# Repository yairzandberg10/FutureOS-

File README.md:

# FutureOS

A custom Android-based OS for a **keys-only feature phone** — no touchscreen anywhere. Base: Android 12 (SDK 31), target device: 640×960px keypad phone (T9 numeric keypad, `\*`/`#`, D-pad nav). Every screen across every app is operable by keypad focus traversal and numeric shortcuts.

Since there's no custom ROM, "System UI" (status bar, lock screen, control center, notification center) is implemented by [FutureUI](FutureUI/) as a set of `AccessibilityService` overlays — the practical way to build a custom system shell on stock Android 12. Design language: dark/glass, Material Symbols Rounded, gradient accents.

## Apps

|Folder|App name|Package|Role|
|-|-|-|-|
|[FutureUI](FutureUI/)|FutureUI|`com.future.futureui`|System UI — status bar, lock screen, control center, notification center|
|[SystemUI](SystemUI/)|System UI|`com.android.sistemui`|A second, parallel implementation of the System UI role — the same six `AccessibilityService`s as FutureUI, plus Do-Not-Disturb scheduling. Not installed on the test device; see the note below|
|[FutureLauncher](FutureLauncher/)|מסך הבית|`com.future.futurelauncher`|Home screen / launcher|
|[Settings](Settings/)|הגדרות|`com.future.settings`|System settings|
|[dialer](dialer/)|טלפון|`com.future.dialer`|Phone dialer|
|[Messages](Messages/)|הודעות|`com.future.messages`|SMS messaging|
|[notes](notes/)|פתקים|`com.future.notes`|Notes|
|[Tasks](Tasks/)|משימות|`com.future.tasks`|Task management - to-do list with priorities|
|[Bluetooth](Bluetooth/)|בלוטוס|`com.future.bluetooth`|Bluetooth device manager - scan, pair, unpair|
|[Calendar](Calendar/)|לוח שנה|`com.future.calendar`|Hebrew calendar, Daf Yomi, location-based zmanim|
|[Contact](Contact/)|אנשי קשר|`com.future.contact`|Contacts|
|[Navigation](Navigation/)|ניווט ותחבורה|`com.future.navigation`|Driving navigation \& public-transit journey planner|
|[Files](Files/)|קבצים|`com.future.files`|File browser|
|[Keyboard](Keyboard/)|מקלדת|`com.future.keyboard`|System-wide T9 predictive text input method|
|[Gallery](Gallery/)|גלריה|`com.future.gallery`|Photo/video gallery|
|[Camera](Camera/)|מצלמה|`com.future.camera`|Camera - live preview, capture, flash, front/back switch|
|[Music](Music/)|מוזיקה|`com.future.music`|Local music player|
|[Sfarim](Sfarim/)|בלכתך בדרך|`com.future.sfarim`|Torah text library|
|[Terminal](Terminal/)|טרמינל|`com.future.terminal`|Root shell terminal|
|[Tools](Tools/)|כלים|`com.future.tools`|Unit converter, QR/text scanner, quick notes, random picker and other small utilities|
|[Flashlight](Flashlight/)|פנס|`com.future.flashlight`|Standalone flashlight — the duplicate inside Tools was removed; FutureUI keeps a torch toggle in the control center, which is the system shell, not a second app|
|[Recorder](Recorder/)|רשמקול|`com.future.recorder`|Voice recorder — records in a foreground service (keeps going with the screen off), live level bars, pause/resume, playback with key seeking, rename/share/delete from the Options menu|
|[Calculator](Calculator/)|מחשבון|`com.future.calculator`|Calculator|
|[Clock](Clock/)|שעון|`com.future.clock`|Alarms, world clock, stopwatch, timer|
|[Fitness](Fitness/)|כושר|`com.future.fitness`|Workout tracking, Bluetooth heart-rate monitor|
|[Remote](Remote/)|שלט|`com.future.remote`|Universal infrared remote (non-TV devices: A/C, fan, audio, custom)|
|[Guide](Guide/)|מדריך למשתמש|`com.future.guide`|On-device user guide for every app|
|[Assistant](Assistant/)|עוזר קולי|`com.future.assistant`|Voice assistant - also opens on a global double-press of OK, see FutureUI|
|[Translate](Translate/)|תרגום|`com.future.translate`|On-device translation (ML Kit), language download for offline use, conversation mode|
|[Wallpapers](Wallpapers/)|רקעים|`com.future.wallpapers`|Wallpaper picker (online catalog). No launcher icon: opens from "Wallpaper" in the launcher's edit mode|

[Frixa](Frixa/) (`com.future.frixa`, recipe catalog and nearby grocery stores) also lives in this repo but is **not part of the system**: it is not in the launcher's built-in app list (`FutureLauncher/DefaultApps.kt`), has no page in the Guide, and holds none of the FutureOS signature permissions.

Two more top-level folders are not standalone apps: [SharedKeypadNav](SharedKeypadNav/) is a shared Gradle library module (`com.future.sharednav`) that **all 30** apps above depend on for D-pad focus handling, T9 digit mapping, and the cross-app design system (colors, spacing, type scale) — see [`SharedKeypadNav/README.md`](SharedKeypadNav/README.md), which is also the canonical design-system reference for this project. [hardware](hardware/) holds CAD files (Onshape motherboard keep-out volumes, an OpenSCAD case/keycap model) for the target device, a Qin F22 Pro.

Each app is a standalone Android Studio project (its own `build.gradle.kts`/`settings.gradle.kts`) living in its own top-level folder here.

## Notes

* `Sfarim/tools/output/sefaria.db` (Torah-text database, ~1.55GB / 6,211 books) is present on disk but **not** tracked in this repo's git — GitHub blocks files over 100MB. It is built directly from Sefaria's public sources via `Sfarim/tools/build_library.py`; see `Sfarim/README.md` for the exact rebuild command. `Sfarim/tools/output/reassemble_sefaria_db.sh` documents an earlier, abandoned plan to split/reassemble a pre-built ~2.1GB copy — no longer needed now that the DB is built from source, but the script is left in place for reference.
* This repo is a fresh consolidation of the individual app projects (no prior per-app git history was carried over).
* **[FutureUI](FutureUI/) and [SystemUI](SystemUI/) both implement the System UI role, and only one of them can be active at a time.** Both declare the same five services (the separate `LockScreenAccessibilityService` was removed on 2026-09-24; FutureUI's lock screen now runs inside its existing services - see `FutureUI/.../lockscreen/` and `LockSettingsActivity` - so a leftover `LockScreenAccessibilityService` entry in `enabled_accessibility_services` on a device is stale and can be removed) — `StatusBarAccessibilityService`, `NotificationCenterAccessibilityService`, `ControlCenterAccessibilityService`, `MediaControlService`, `HeadsUpNotificationService` — under different package names (`com.future.futureui` vs `com.android.sistemui`; the latter is spelled "sistemui" because `com.android.systemui` is a reserved system package and cannot be installed). Enabling both sets of `AccessibilityService`s would make two overlay stacks compete for the same key events, and the status bar service in particular swallows `KEYCODE_MENU`/`KEYCODE_SETTINGS` system-wide, so a duplicate would break the Options key everywhere. On the `F22 Pro` test device only FutureUI is installed and its three overlay services are the ones enabled. Which of the two is intended to win long-term is not recorded anywhere in this repo.

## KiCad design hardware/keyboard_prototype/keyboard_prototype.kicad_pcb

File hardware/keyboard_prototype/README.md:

# FutureOS Keyboard Prototype - מה יש כאן ואיך מזמינים

אב-טיפוס USB של מקלדת FutureOS: ‏21 מקשים, מטריצה 5×5 ותאורה אחורית. הלוח נשלט על ידי XIAO RP2040 **לבדיקה בלבד**, וה-XIAO אינו חלק מהחומרה הסופית של FutureOS Regular.

## הקבצים

| קובץ | מה זה |
|---|---|
| `keyboard_prototype.kicad_pro` | הפרויקט. פותחים אותו ב-KiCad 10 |
| `keyboard_prototype_schematic.pdf` | הסכמה |
| `fab/keyboard_prototype_gerbers.zip` | **הקובץ שמעלים למפעל** (לוח) |
| `fab/BOM_JLCPCB.csv`, `fab/CPL_JLCPCB.csv` | קבצים להרכבת הרכיבים במפעל |
| `fab/keyboard_prototype.step` | מודל תלת-ממדי, להכנסה לגוף ב-CAD |
| `render/pcb_top.png`, `pcb_bottom.png`, `pcb_3d.png` | תמונות של הלוח |
| `firmware/` | הקושחה ל-XIAO וקובץ מיפוי המקשים ל-Android |
| `SPEC.md` | המפרט המאושר |
| `tools/design.py` + `build.sh` | מחולל פרמטרי: משנים את `design.py` ומריצים `./build.sh` |

## הזמנה מ-JLCPCB (10 לוחות)

1. ב-jlcpcb.com בוחרים **Order now** ומעלים את `fab/keyboard_prototype_gerbers.zip`.
2. בוחרים את ההגדרות: 2 שכבות, **עובי 1.0 מ"מ**, כמות 10, וכל השאר בברירת מחדל.
3. מסמנים **PCB Assembly**, צד **Top**, ומעלים את `BOM_JLCPCB.csv` ואת `CPL_JLCPCB.csv`.
4. במסך ה-preview בודקים שכל רכיב יושב על הפדים שלו. **כדאי לבדוק במיוחד את כיוון הדיודות והנורות.** אם משהו מסובב, מתקנים את הסיבוב שם, בממשק של JLC.
5. את ה-XIAO RP2040 קונים בנפרד (Seeed, כ-5 דולר ליחידה). המפעל לא מרכיב אותו.

## הרכבה ידנית (אחרי שהלוחות מגיעים)

1. **ה-XIAO**: מולחם שטוח בצד האחורי, כשהרכיבים שלו פונים החוצה וה-USB-C פונה לקצה התחתון, בהתאם לסימון ה-"USB-C" על הלוח. מלחימים רק את 14 הפדים שבצדדים, ולא את הפדים שמתחתיו.
2. **JP1**: מחברים את שני חצאי הגשר בטיפת בדיל. בלי זה התאורה לא תדלק מה-USB.
3. **J1 (FPC)** לא נדרש לבדיקה עם ה-XIAO. **לא מחברים כבל FPC כשה-XIAO מולחם.**

## הפעלה

1. מחזיקים את כפתור BOOT ב-XIAO ומחברים אותו למחשב. מופיע כונן בשם RPI-RP2.
2. גוררים לכונן קובץ UF2 של CircuitPython ל-XIAO RP2040 מאתר circuitpython.org. אחרי זה מופיע כונן בשם CIRCUITPY.
3. מעתיקים לכונן את `firmware/boot.py` ואת `firmware/code.py`, ומנתקים ומחברים מחדש.
4. במכשיר Android עם root, מתקינים את `firmware/Vendor_1209_Product_0001.kl` לפי ההוראות שבראש הקובץ.
5. מחברים את המקלדת לטלפון דרך OTG.

## מה לבדוק (תכתוב לי את התוצאות)

- כל 21 המקשים: כל מקש שולח את הקוד שכתוב בטבלה ב-`SPEC.md`.
- לחיצה על שני מקשים יחד מזהה את שניהם, בלי "רפאים".
- התאורה נדלקת בלחיצה ונכבית אחרי 8 שניות.

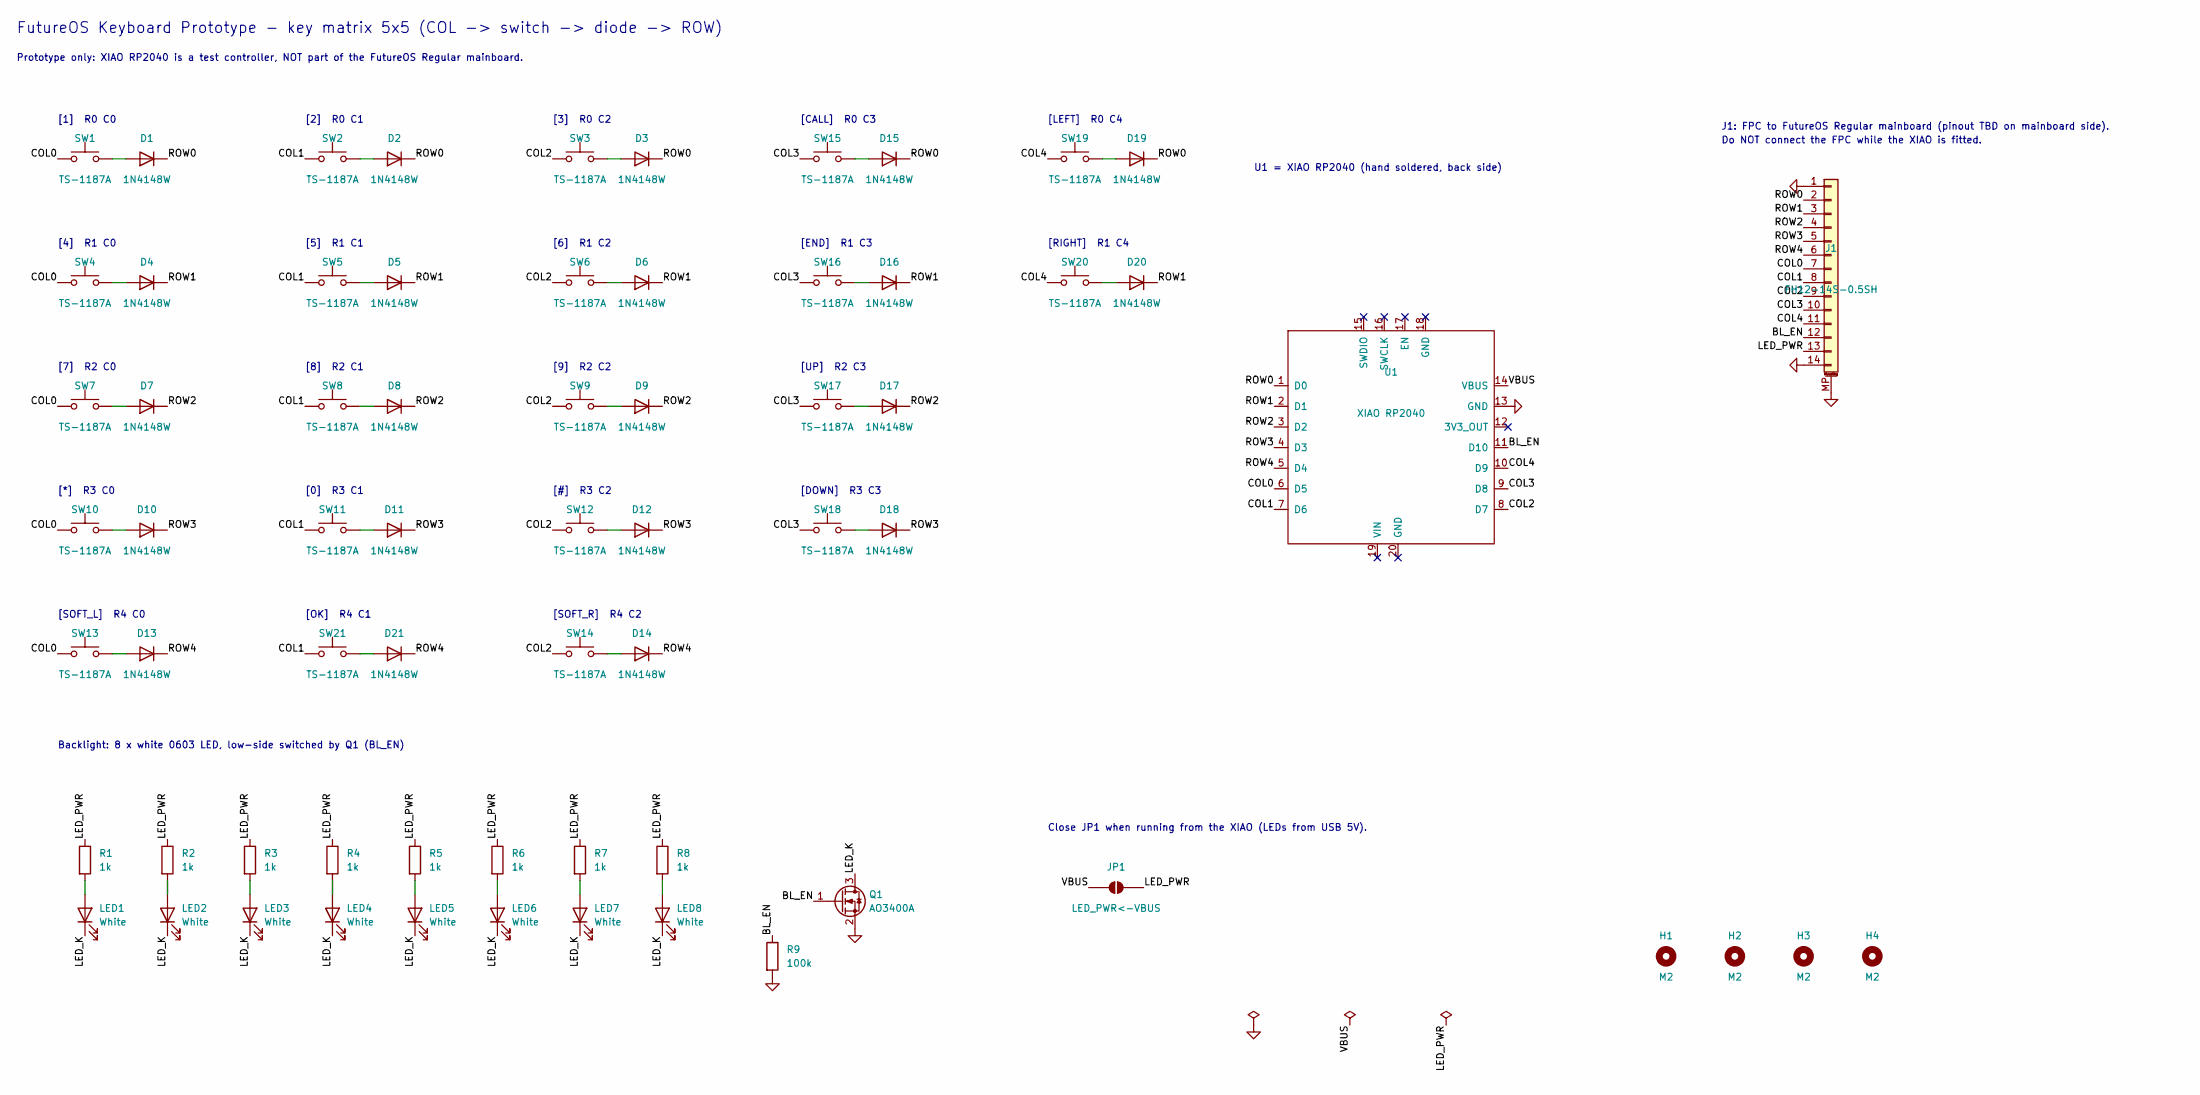
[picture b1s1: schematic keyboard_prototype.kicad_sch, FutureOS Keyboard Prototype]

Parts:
D1, D2, D3, D4, D5, D6, D7, D8, D9, D10, D11, D12, D13, D14, D15, D16, D17, D18, D19, D20, D21: 1N4148W; D_SOD-123
H1, H2, H3, H4: M2; MountingHole_2.2mm_M2
J1: FH12-14S-0.5SH; Hirose_FH12-14S-0.5SH_1x14-1MP_P0.50mm_Horizontal
JP1: LED_PWR<-VBUS; SolderJumper-2_P1.3mm_Open_Pad1.0x1.5mm
LED1, LED2, LED3, LED4, LED5, LED6, LED7, LED8: White; LED_0603_1608Metric
Q1: AO3400A; SOT-23
R1, R2, R3, R4, R5, R6, R7, R8: 1k; R_0603_1608Metric
R9: 100k; R_0603_1608Metric
SW1, SW2, SW3, SW4, SW5, SW6, SW7, SW8, SW9, SW10, SW11, SW12, SW13, SW14, SW15, SW16, SW17, SW18, SW19, SW20, SW21: TS-1187A; SW_Push_1P1T_XKB_TS-1187A
U1: XIAO RP2040; XIAO-RP2040-SMD

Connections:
/BL_EN: J1.12, Q1.1 (G), R9.1, U1.11 (D10)
/COL0: J1.7, SW1.1, SW4.1, SW7.1, SW10.1, SW13.1, U1.6 (D5)
/COL1: J1.8, SW2.1, SW5.1, SW8.1, SW11.1, SW21.1, U1.7 (D6)
/COL2: J1.9, SW3.1, SW6.1, SW9.1, SW12.1, SW14.1, U1.8 (D7)
/COL3: J1.10, SW15.1, SW16.1, SW17.1, SW18.1, U1.9 (D8)
/COL4: J1.11, SW19.1, SW20.1, U1.10 (D9)
/LED_K: LED1.1 (K), LED2.1 (K), LED3.1 (K), LED4.1 (K), LED5.1 (K), LED6.1 (K), LED7.1 (K), LED8.1 (K), Q1.3 (D)
/LED_PWR: J1.13, JP1.2 (B), R1.1, R2.1, R3.1, R4.1, R5.1, R6.1, R7.1, R8.1
/ROW0: D1.1 (K), D2.1 (K), D3.1 (K), D15.1 (K), D19.1 (K), J1.2, U1.1 (D0)
/ROW1: D4.1 (K), D5.1 (K), D6.1 (K), D16.1 (K), D20.1 (K), J1.3, U1.2 (D1)
/ROW2: D7.1 (K), D8.1 (K), D9.1 (K), D17.1 (K), J1.4, U1.3 (D2)
/ROW3: D10.1 (K), D11.1 (K), D12.1 (K), D18.1 (K), J1.5, U1.4 (D3)
/ROW4: D13.1 (K), D14.1 (K), D21.1 (K), J1.6, U1.5 (D4)
/VBUS: JP1.1 (A), U1.14 (VBUS)
GND: J1.1, J1.14, J1.MP (MountPin), Q1.2 (S), R9.2, U1.13 (GND)
unnamed: D1.2 (A), SW1.2
unnamed: D2.2 (A), SW2.2
unnamed: D3.2 (A), SW3.2
unnamed: D4.2 (A), SW4.2
unnamed: D5.2 (A), SW5.2
unnamed: D6.2 (A), SW6.2
unnamed: D7.2 (A), SW7.2
unnamed: D8.2 (A), SW8.2
unnamed: D9.2 (A), SW9.2
unnamed: D10.2 (A), SW10.2
unnamed: D11.2 (A), SW11.2
unnamed: D12.2 (A), SW12.2
unnamed: D13.2 (A), SW13.2
unnamed: D14.2 (A), SW14.2
unnamed: D15.2 (A), SW15.2
unnamed: D16.2 (A), SW16.2
unnamed: D17.2 (A), SW17.2
unnamed: D18.2 (A), SW18.2
unnamed: D19.2 (A), SW19.2
unnamed: D20.2 (A), SW20.2
unnamed: D21.2 (A), SW21.2
unnamed: LED1.2 (A), R1.2
unnamed: LED2.2 (A), R2.2
unnamed: LED3.2 (A), R3.2
unnamed: LED4.2 (A), R4.2
unnamed: LED5.2 (A), R5.2
unnamed: LED6.2 (A), R6.2
unnamed: LED7.2 (A), R7.2
unnamed: LED8.2 (A), R8.2

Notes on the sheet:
FutureOS Keyboard Prototype - key matrix 5x5 (COL -> switch -> diode -> ROW)
Prototype only: XIAO RP2040 is a test controller, NOT part of the FutureOS Regular mainboard.
[1] R0 C0
[2] R0 C1
[3] R0 C2
[4] R1 C0
[5] R1 C1
[6] R1 C2
[7] R2 C0
[8] R2 C1
[9] R2 C2
[*] R3 C0
[0] R3 C1
[#] R3 C2
[SOFT_L] R4 C0
[SOFT_R] R4 C2
[CALL] R0 C3
[END] R1 C3
[UP] R2 C3
[DOWN] R3 C3
[LEFT] R0 C4
[RIGHT] R1 C4
[OK] R4 C1
U1 = XIAO RP2040 (hand soldered, back side)
J1: FPC to FutureOS Regular mainboard (pinout TBD on mainboard side).
Do NOT connect the FPC while the XIAO is fitted.
Backlight: 8 x white 0603 LED, low-side switched by Q1 (BL_EN)
Close JP1 when running from the XIAO (LEDs from USB 5V).

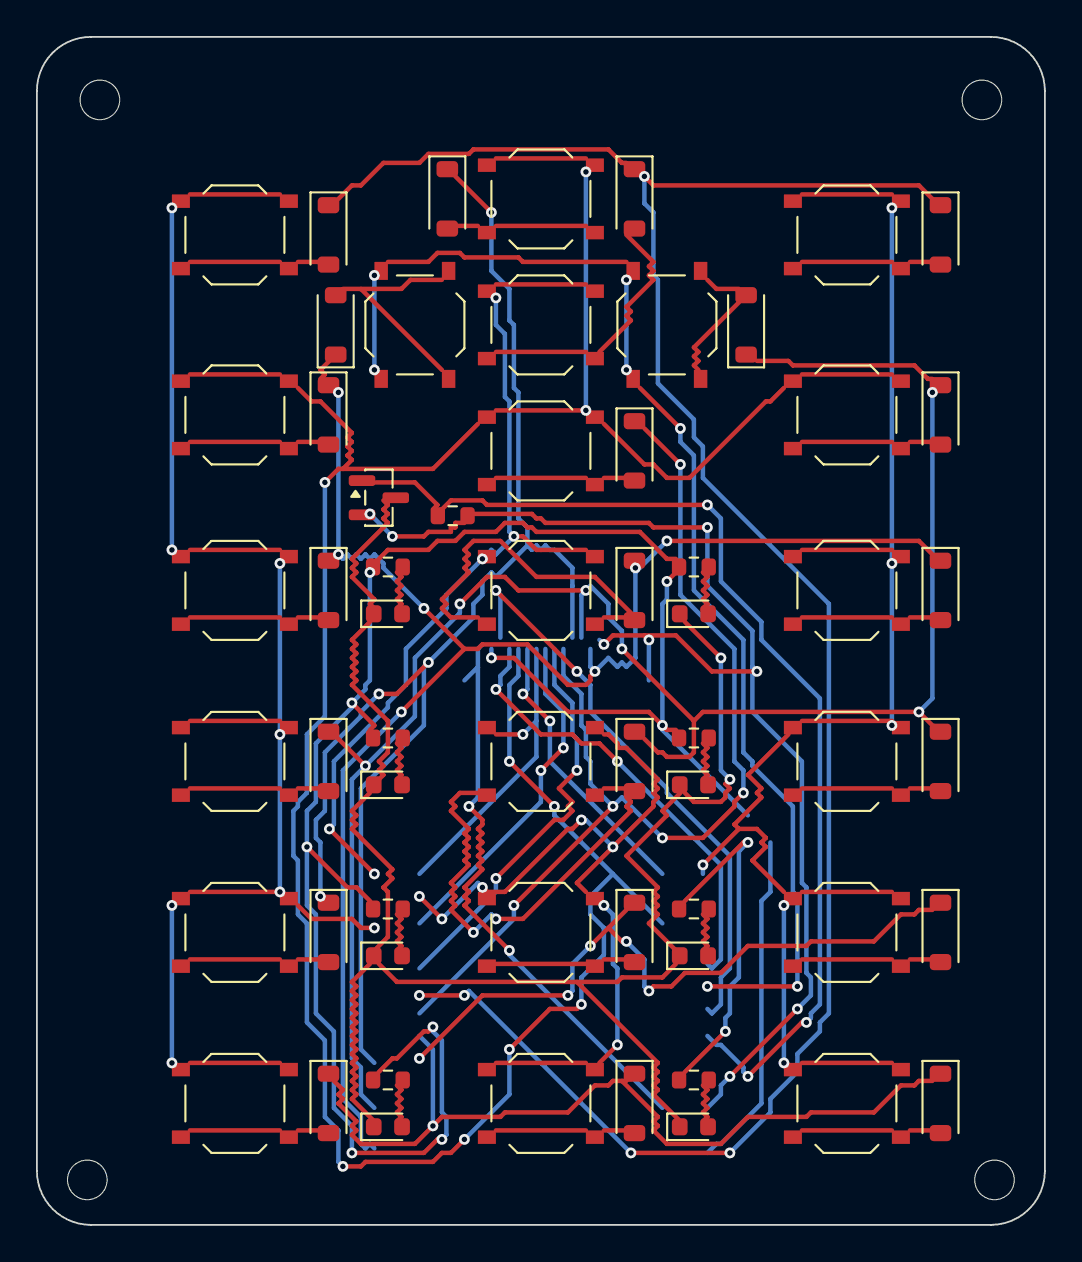
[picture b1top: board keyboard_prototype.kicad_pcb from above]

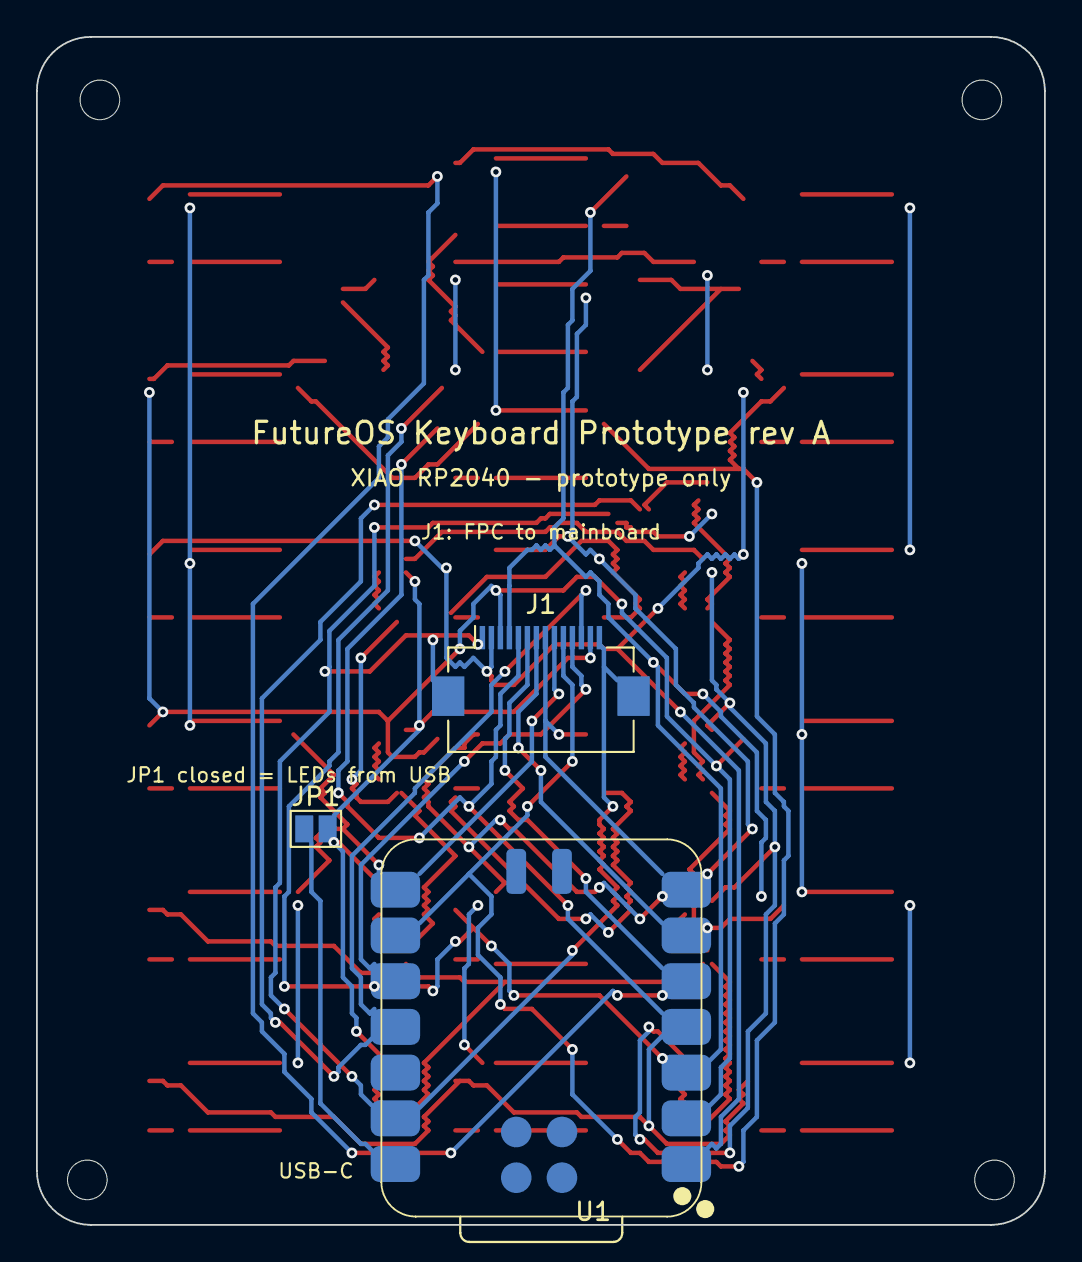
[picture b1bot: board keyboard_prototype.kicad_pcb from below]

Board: 2 copper layers, 56.0 x 66.0 mm, 67 parts (3 on the bottom side), 44 nets.

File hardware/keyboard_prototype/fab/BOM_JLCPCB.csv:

Comment,Designator,Footprint,LCSC,MPN
100k,R9,R_0603_1608Metric,C25803,UNI-ROYAL 0603WAF1003T5E
1N4148W,"D1,D2,D3,D4,D5,D6,D7,D8,D9,D10,D11,D12,D13,D14,D15,D16,D17,D18,D19,D20,D21",D_SOD-123,C81598,1N4148W
1k,"R1,R2,R3,R4,R5,R6,R7,R8",R_0603_1608Metric,C21190,UNI-ROYAL 0603WAF1001T5E
AO3400A,Q1,SOT-23,C20917,AOS AO3400A
TS-1187A,"SW1,SW2,SW3,SW4,SW5,SW6,SW7,SW8,SW9,SW10,SW11,SW12,SW13,SW14,SW15,SW16,SW17,SW18,SW19,SW20,SW21",SW_Push_1P1T_XKB_TS-1187A,C318884,XKB TS-1187A-B-A-B
White,"LED1,LED2,LED3,LED4,LED5,LED6,LED7,LED8",LED_0603_1608Metric,C2290,KENTO KT-0603W

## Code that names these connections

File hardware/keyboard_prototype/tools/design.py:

"""FutureOS Keyboard Prototype - single source of truth for the design.

Board coordinates: mm, origin = board bottom-left seen from the FRONT, Y up
(toward the screen). Values come from hardware/openscad/futureos_family.scad
with MODEL=regular (board bottom edge = 3 mm above the body bottom).
See ../SPEC.md for the approved spec.
"""
import os

KICAD = r"C:/Users/yairz/AppData/Local/Programs/KiCad/10.0"
SYMS = KICAD + "/share/kicad/symbols/"
FPS = KICAD + "/share/kicad/footprints/"
HERE = os.path.dirname(os.path.abspath(__file__))
PROJ_DIR = os.path.dirname(HERE)
PROJECT = "keyboard_prototype"
LOCAL_FP_LIB = "keyboard_prototype"  # project-local .pretty (XIAO footprint from Seeed)

# --- mechanics (from futureos_family.scad, MODEL=regular) -------------------
BOARD_W, BOARD_H, BOARD_R = 56.0, 66.0, 3.0
BOARD_T = 1.0
KEY_P, ROW_P = 17.0, 9.5          # column / digit-row pitch
DPAD_R = 7.0                      # D-pad switch radius from OK
CX = BOARD_W / 2
NAV_Y = 50.0                      # D-pad centre
HOLES = [(2.8, 2.5), (53.2, 2.5), (3.5, 62.5), (52.5, 62.5)]

# --- keys: (label, x, y, rot, row, col, android keycode) --------------------
_digit_rows = [("1", "2", "3"), ("4", "5", "6"), ("7", "8", "9"), ("*", "0", "#")]
_digit_y = [35.25, 25.75, 16.25, 6.75]
_codes = {"*": "STAR", "#": "POUND"}

KEYS = []
for r, (labels, y) in enumerate(zip(_digit_rows, _digit_y)):
    for c, lab in enumerate(labels):
        KEYS.append((lab, CX + (c - 1) * KEY_P, y, 0, r, c, "KEYCODE_" + _codes.get(lab, lab)))
KEYS += [
    ("SOFT_L", CX - KEY_P, 55.0, 0, 4, 0, "KEYCODE_MENU"),
    ("SOFT_R", CX + KEY_P, 55.0, 0, 4, 2, "KEYCODE_BACK"),
    ("CALL",   CX - KEY_P, 45.0, 0, 0, 3, "KEYCODE_CALL"),
    ("END",    CX + KEY_P, 45.0, 0, 1, 3, "KEYCODE_ENDCALL"),
    ("UP",     CX, NAV_Y + DPAD_R, 0, 2, 3, "KEYCODE_DPAD_UP"),
    ("DOWN",   CX, NAV_Y - DPAD_R, 0, 3, 3, "KEYCODE_DPAD_DOWN"),
    ("LEFT",   CX - DPAD_R, NAV_Y, 90, 0, 4, "KEYCODE_DPAD_LEFT"),
    ("RIGHT",  CX + DPAD_R, NAV_Y, 90, 1, 4, "KEYCODE_DPAD_RIGHT"),
    ("OK",     CX, NAV_Y, 0, 4, 1, "KEYCODE_DPAD_CENTER"),
]
assert len(KEYS) == 21
assert len({(k[4], k[5]) for k in KEYS}) == 21, "matrix position used twice"

# --- XIAO RP2040 pin map (pad numbers from Seeed XIAO-RP2040-SMD footprint) --
# pad: (XIAO name, net)
XIAO_PINS = {
    "1": ("D0", "ROW0"), "2": ("D1", "ROW1"), "3": ("D2", "ROW2"), "4": ("D3", "ROW3"),
    "5": ("D4", "ROW4"), "6": ("D5", "COL0"), "7": ("D6", "COL1"), "8": ("D7", "COL2"),
    "9": ("D8", "COL3"), "10": ("D9", "COL4"), "11": ("D10", "BL_EN"),
    "12": ("3V3_OUT", None), "13": ("GND", "GND"), "14": ("VBUS", "VBUS"),
    # pads under the module (SWD / battery) - not used, left unsoldered
    "15": ("SWDIO", None), "16": ("SWCLK", None), "17": ("EN", None),
    "18": ("GND", None), "19": ("VIN", None), "20": ("GND", None),
}
RP2040_GPIO = {"D0": 26, "D1": 27, "D2": 28, "D3": 29, "D4": 6, "D5": 7,
               "D6": 0, "D7": 1, "D8": 2, "D9": 4, "D10": 3}

# --- FPC J1 pinout (our definition; mainboard side TBD) ----------------------
FPC_PINS = ["GND", "ROW0", "ROW1", "ROW2", "ROW3", "ROW4",
            "COL0", "COL1", "COL2", "COL3", "COL4", "BL_EN", "LED_PWR", "GND"]

N_LEDS = 8
LED_R = "1k"

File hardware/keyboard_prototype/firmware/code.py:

# FutureOS Keyboard Prototype - CircuitPython firmware for Seeed XIAO RP2040
#
# 5x5 key matrix (21 keys) -> USB HID keyboard. No extra libraries needed:
# HID reports are sent raw through usb_hid.
#
# Matrix wiring (see ../SPEC.md): COL -> switch -> diode (anode) -> ROW
#   ROW0..ROW4 = D0..D4, COL0..COL4 = D5..D9, backlight enable = D10
#
# On Android the keys arrive as normal keyboard keys. The special keys
# (*, #, Call, End, Options, Back, OK) are sent as F1..F6 / Enter and
# remapped to the FutureOS keycodes by Vendor_1209_Product_0001.kl.

import time

import board
import keypad
import pwmio
import usb_hid

ROWS = (board.D0, board.D1, board.D2, board.D3, board.D4)
COLS = (board.D5, board.D6, board.D7, board.D8, board.D9)

# HID usage IDs (USB HID Usage Tables, Keyboard page 0x07)
K1, K2, K3, K4, K5, K6, K7, K8, K9, K0 = 0x1E, 0x1F, 0x20, 0x21, 0x22, 0x23, 0x24, 0x25, 0x26, 0x27
ENTER = 0x28
F1, F2, F3, F4, F5, F6 = 0x3A, 0x3B, 0x3C, 0x3D, 0x3E, 0x3F
RIGHT, LEFT, DOWN, UP = 0x4F, 0x50, 0x51, 0x52

#            COL0  COL1   COL2  COL3  COL4
KEYMAP = (
    (K1,   K2,    K3,   F3,   LEFT),   # ROW0: 1 2 3 CALL LEFT
    (K4,   K5,    K6,   F4,   RIGHT),  # ROW1: 4 5 6 END  RIGHT
    (K7,   K8,    K9,   UP,   None),   # ROW2: 7 8 9 UP
    (F1,   K0,    F2,   DOWN, None),   # ROW3: * 0 # DOWN
    (F5,   ENTER, F6,   None, None),   # ROW4: SOFT_L OK SOFT_R
)

BACKLIGHT_TIMEOUT = 8.0   # seconds after the last key press
BACKLIGHT_LEVEL = 0.6     # 0..1

matrix = keypad.KeyMatrix(row_pins=ROWS, column_pins=COLS, columns_to_anodes=True)
keyboard = next(d for d in usb_hid.devices if d.usage_page == 0x01 and d.usage == 0x06)
backlight = pwmio.PWMOut(board.D10, frequency=1000, duty_cycle=0)

pressed = []
report = bytearray(8)
last_activity = time.monotonic()


def send():
    report[0] = 0
    for i in range(6):
        report[2 + i] = pressed[i] if i < len(pressed) else 0
    try:
        keyboard.send_report(report)
    except OSError:
        pass  # USB not ready yet


def set_backlight(on):
    backlight.duty_cycle = int(65535 * BACKLIGHT_LEVEL) if on else 0


set_backlight(True)

while True:
    event = matrix.events.get()
    now = time.monotonic()
    if event:
        row, col = divmod(event.key_number, len(COLS))
        code = KEYMAP[row][col]
        if code is not None:
            if event.pressed and code not in pressed:
                pressed.append(code)
            elif event.released and code in pressed:
                pressed.remove(code)
            send()
        last_activity = now
        set_backlight(True)
    elif now - last_activity > BACKLIGHT_TIMEOUT:
        set_backlight(False)
    time.sleep(0.002)
